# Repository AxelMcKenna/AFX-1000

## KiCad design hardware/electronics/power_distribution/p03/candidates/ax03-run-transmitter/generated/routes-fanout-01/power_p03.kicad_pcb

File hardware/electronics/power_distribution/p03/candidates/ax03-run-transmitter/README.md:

# P03 AX03 RUN transmitter candidate

The preferred 264-part paired project has zero native DRC errors, warnings,
opens, ERC and parity findings with every rule category enabled. It is not
physically qualified or released for fabrication.

Use [CURRENT_LAYOUT.json](CURRENT_LAYOUT.json) or the
[checked project](generated/native-closed-transmitter/power_p03.kicad_pro).
The root PCB is an incomplete staging parent.

The [integration review](../../../../../qualification/boards/aux_low_power_run/P03_INTEGRATION_REVIEW.md)
documents exact source conservation, actual local bypass paths, five new
via-in-SMD process requirements, the four-wire logical E28 map and outstanding
qualification. The
[actual PCB plot](generated/native-closed-transmitter/closed-top.svg),
[native results](generated/native-closed-transmitter/review.json) and
[handoff](generated/native-closed-transmitter/handoff.json) retain the evidence.

The eight-part source cell buffers only J106.3. Original R113, internal RUN/PG
and switch topology remain intact. The original 160 × 45 mm outline, mounting
positions, stackup and all 1,254 strict-source vias remain exact. The strict
source's two P19_SRC neck limitations and all manufacturing/physical holds carry
forward. Canonical and preserved source projects are unchanged.

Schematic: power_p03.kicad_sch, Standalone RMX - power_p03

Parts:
C1, C63: 10uF 63V X7R; C_1210_3225Metric
C2, C3, C5, C6, C8, C9, C37, C42, C52, C57, C64, C65, C67, C68, C70, C204, C205, C224, C225, C254: 22uF 50V X7R 20% TDK C3225X7R1H226M250AC; C_1210_3225Metric
C4, C7, C10, C35, C38, C40, C43, C50, C53, C55, C58, C59, C61, C66, C69, C71: 100nF 50V X7R; C_0805_2012Metric
C11, C30, C107, C108: 100nF 16V X7R; C_0805_2012Metric
C12, C14, C73, C75: 68pF 50V C0G 5%; C_0805_2012Metric
C13, C15, C74, C76: 330nF 16V X7R; C_0805_2012Metric
C31: 2.2uF 16V X7R; C_0805_2012Metric
C32, C33: 1uF film 63V 10% MKS2C041001F00KSSD; C_Rect_L7.2mm_W5.0mm_P5.00mm
C34, C39, C49, C54, C240: 47nF 50V C0G 5%; C_1210_3225Metric
C36, C41, C51, C56: 10uF 50V X7R; C_1210_3225Metric
C60, C62, C105: 1uF 50V X7R; C_0805_2012Metric
C72, C210, C211, C230, C231: 100nF 50V X7R 10% TDK C1005X7R1H104K050BB; C_0402_1005Metric
C101, C102: 2.2uF 100V X7R; C_1210_3225Metric
C103: 220uF 35V electrolytic 20% (EEUFR1V221); CP_Radial_D8.0mm_P3.50mm
C104: 1uF 50V X7R; C_1210_3225Metric
C106: 10uF 25V X7R 10% TDK C3225X7R1E106K250AC; C_1210_3225Metric
C109: 1nF 16V C0G 5%; C_0805_2012Metric
C110: 10nF 25V C0G 5% KEMET C0603C103J3GACTU; C_0603_1608Metric
C113: 1uF 100V X7S 10% TDK C2012X7S2A105K125AE; C_0805_2012Metric
C200, C220: 4.7uF 25V X7R 10% TDK C2012X7R1E475K125AB; C_0805_2012Metric
C201, C221, C255, C301, C302: 100nF 50V X7R; C_0603_1608Metric
C202, C203, C222, C223: 2.2uF 50V X7R 10% TDK C2012X7R1H225K125AC; C_0805_2012Metric
C206, C207, C208, C209, C226, C227, C228, C229: 47uF 25V X7S 20% TDK C3225X7S1E476M250AC; C_1210_3225Metric
C241: 1uF 25V X7R; C_1210_3225Metric
C242, C243, C244, C245, C246, C247, C248, C249, C250, C251: 100nF 25V C0G 5% KEMET C1206C104J3GACTU; C_1206_3216Metric
C252, C253: 1uF 16V X7R; C_1210_3225Metric
C300: 10nF 50V C0G 5%; C_0805_2012Metric
C401, C402: 100nF 50V X7R C0603C104K5RACTU; C0603
C403: 10nF 50V C0G C0603C103J5GACTU; C0603
D1, D2, D3, D4, D103: SS16-E3/61T; D_SMA
D101: SMBJ33CA-E3/52; D_SMB
D102: BAS116,215; SOT-23
J2: Header6; PinHeader_1x06_P2.54mm_Vertical
J3: Header2; PinHeader_1x02_P2.54mm_Vertical
J20, J21, J23, J24: Wurth 7466003R M3 SMT; Wurth_7466003R
J22: P03 READY test; PinHeader_1x03_P2.54mm_Vertical
J101: JST B2PS-VH (VHR-2N/SVH-41T-P1.1 AWG16); JST_VH_B2PS-VH_1x02_P3.96mm_Horizontal
J103: Bare POWER_READY probe pads, no fitted header; Probe2_P2.54_D1
J104: JST B3B-XH-A (XHP-3/SXH-001T-P0.6); JST_XH_B3B-XH-A_1x03_P2.50mm_Vertical
J106: JST B4B-XH-A (XHP-4/SXH-001T-P0.6); JST_XH_B4B-XH-A_1x04_P2.50mm_Vertical
L1, L6: 33uH 20% SRP7050WA-330M; SRP7050WA
L2, L3, L7, L8: 68uH 20% SRP1050WA-680M; SRP1050WA
L20, L23: 4.7uH 20% Coilcraft XAL7030-472MEC; L_Coilcraft_XAL7030-472
Q101: PSMN012-100YL,115; LFPAK56
Q102: BSS138-7-F; SOT-23
Q103: DMN2056U-7; SOT-23
R1: 300k 0.01% 5ppm; R_0805_2012Metric
R2, R3, R4, R45, R46: 15k 0.01% 5ppm; R_0805_2012Metric
R5, R20, R21, R34, R35: 330k 0.01% 5ppm; R_0805_2012Metric
R6, R7, R49, R50: 4.7k 1%; R_0805_2012Metric
R17, R19, R110: 1k 1%; R_0805_2012Metric
R18, R120: 100k 1%; R_0805_2012Metric
R22, R27, R36, R41, R243, R244: 100k 0.01% 5ppm; R_0805_2012Metric
R23, R28, R37, R42, R241: 6.8k 1%; R_0805_2012Metric
R24, R38: 9.09k 1%; R_0805_2012Metric
R25, R39, R47, R306: 200k 0.01% 5ppm; R_0805_2012Metric
R26, R40, R308: 180k 0.01% 5ppm; R_0805_2012Metric
R29, R43: 5.62k 1%; R_0805_2012Metric
R44: 240k 0.01% 5ppm; R_0805_2012Metric
R48, R301, R303, R305, R307, R309, R314: 10k 0.01% 5ppm; R_0805_2012Metric
R101, R103, R117: 309k 0.1% 10ppm; R_0805_2012Metric
R102: 40.2k 0.1% 10ppm; R_0805_2012Metric
R104: 28k 0.1% 10ppm; R_0805_2012Metric
R105: 68.1k 0.1% 10ppm; R_0805_2012Metric
R106, R109, R118, R119: 10k 0.1% 10ppm; R_0805_2012Metric
R107: 4.02k 0.1% 10ppm; R_0805_2012Metric
R108: 11.7k 0.1% 10ppm; R_0805_2012Metric
R111, R204, R224, R246: 10k 1%; R_0805_2012Metric
R112, R114: 47k 1%; R_0805_2012Metric
R113: 3.3k 1%; R_0805_2012Metric
R115: 30.9k 0.1% 10ppm; R_0805_2012Metric
R116: 3.09k 0.1% 10ppm; R_0805_2012Metric
R121: 100 1%; R_0805_2012Metric
R130: 49.9 0.01% 5ppm; R_0805_2012Metric
R200: 9k 0.01% 2ppm Susumu RG2012L-902-L-T1; R_0805_2012Metric
R201: 1k 0.01% 2ppm Susumu RG2012L-102-L-T1; R_0805_2012Metric
R202, R222: 24.3k 1%; R_0805_2012Metric
R203, R223: 18.2k 0.1% 25ppm Panasonic ERA6AEB1822V; R_0805_2012Metric
R205, R225: 22k 1%; R_0805_2012Metric
R206: 54.9 0.1% 25ppm Panasonic ERA6AEB549V; R_0805_2012Metric
R220: 11k 0.01% 5ppm; R_0805_2012Metric
R221, R311: 1k 0.01% 5ppm; R_0805_2012Metric
R240: 100 0.01% 5ppm; R_0805_2012Metric
R242: 120 0.01% 5ppm; R_0805_2012Metric
R245: 2.21k 1%; R_0805_2012Metric
R300, R302: 87.6k 0.01% 5ppm; R_0805_2012Metric
R304: 324k 0.01% 5ppm; R_0805_2012Metric
R310: 590 0.01% 5ppm; R_0805_2012Metric
R312: 7.5k 0.01% 5ppm; R_0805_2012Metric
R313: 1M 0.01% 5ppm; R_0805_2012Metric
R315: 750k 0.01% 5ppm; R_0805_2012Metric
R316: 2.2k 0.1% 25ppm Panasonic ERA6AEB222V; R_0805_2012Metric
R401: 100k ohm TNPW0805100KBEEA; R0805
R402: 10M 1% CRCW080510M0FKEA; R0805
R403: 1k 1% CRCW12061K00FKEA; R1206
U1, U13: LT3471EDD#PBF; DFN-10-1EP_3x3mm_P0.5mm_EP1.65x2.38mm
U4: REF5025EIDR; SOIC-8_3.9x4.9mm_P1.27mm
U5: OPA4192ID; SOIC-14_3.9x8.7mm_P1.27mm
U6, U24: OPA2192ID; SOIC-8_3.9x4.9mm_P1.27mm
U7: LT3080IMS8E#PBF; MSOP-8-1EP_3x3mm_P0.65mm_EP1.68x1.88mm
U8: LT3080IQ#PBF; TO-263-5_TabPin3
U10, U11: LT3090IDD#PBF; DFN-10-1EP_3x3mm_P0.5mm_EP1.65x2.38mm
U12: LT1634AIS8-2.5#PBF; SOIC-8_3.9x4.9mm_P1.27mm
U20, U23: TPS543620RPYR; TPS543620_RPY0014A
U21: ADR4550BRZ; SOIC-8_3.9x4.9mm_P1.27mm
U22: LT3045IDD#PBF; DFN-10-1EP_3x3mm_P0.5mm_EP1.65x2.38mm
U25: LTC2910HGN#PBF; SSOP-16_3.9x4.9mm_P0.635mm
U26: SN74LVC1G97DBVR; SOT-23-6
U101: TPS26630RGER; Texas_RGE0024H_VQFN-24-1EP_4x4mm_P0.5mm_EP2.7x2.7mm
U102: TPS7A1601DGNR; MSOP-8-1EP_3x3mm_P0.65mm_EP1.68x1.88mm
U103: TLV7011DBVR; SOT-23-5
U201: TPS389001DSET; TI_DSE0006A
U202: SN74AUP1G17DCKR; TI_DCK0005A

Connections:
/5V_DIG_SRC: C30.1, C206.1 (+), C207.1 (+), C208.1 (+), C209.1 (+), J3.1 (5V_DIG), J23.1, L20.2 (OUT), R6.1, R7.1, R49.1, R50.1, R200.1, R300.1, U4.1 (EN), U4.2 (VIN), U10.5 (SHDN), U11.5 (SHDN)
/AGND: C2.2, C3.2, C4.2, C5.2, C6.2, C7.2, C8.2, C9.2, C10.2, C11.2, C13.2, C15.2, C30.2, C31.2, C32.2, C33.2, C35.2, C36.2, C37.2, C38.2, C40.2, C41.2, C42.2, C43.2, C50.2, C51.2, C52.2, C53.2, C55.2, C56.2, C57.2, C58.2, C59.2, C60.2, C61.2, C62.2, C64.2, C65.2, C66.2, C67.2, C68.2, C69.2, C70.2, C71.2, C72.2, C74.2, C76.2, C101.2 (-), C102.2 (-), C103.2 (-), C104.2 (-), C105.2 (-), C106.2 (-), C107.2 (-), C108.2 (-), C109.2 (-), C110.2 (-), C113.2 (-), C200.2 (-), C202.2 (-), C203.2 (-), C204.2 (-), C205.2 (-), C206.2 (-), C207.2 (-), C208.2 (-), C209.2 (-), C210.2 (-), C211.2 (-), C220.2 (-), C222.2 (-), C223.2 (-), C224.2 (-), C225.2 (-), C226.2 (-), C227.2 (-), C228.2 (-), C229.2 (-), C230.2 (-), C231.2 (-), C241.2 (-), C242.2 (-), C243.2 (-), C244.2 (-), C245.2 (-), C246.2 (-), C247.2 (-), C248.2 (-), C249.2 (-), C250.2 (-), C251.2 (-), C252.2 (-), C253.2 (-), C254.2 (-), C255.2 (-), C300.2 (-), C301.2 (-), C302.2 (-), C401.2, C402.2, C403.2, D2.1 (K), D4.1 (K), D101.2, D103.2 (ANODE), J2.2 (AGND), J3.2 (AGND), J20.1, J21.1, J22.2 (AGND), J101.2 (AGND), J103.1 (AGND), J104.3 (AGND), J106.2 (AGND), Q103.2 (SOURCE), R3.2, R22.2, R24.2, R27.2, R29.2, R36.2, R38.2, R41.2, R43.2, R45.2, R102.2, R104.2, R106.2, R107.2, R109.2, R111.2, R112.2, R114.2, R116.2, R119.2, R120.2, R201.2, R202.2, R203.2, R205.2, R221.2, R222.2, R223.2, R225.2, R243.2, R245.2, R301.2, R303.2, R305.2, R307.2, R309.2, R311.2, R402.2, U1.5 (FB2N), U1.11 (GND_EP), U4.4 (GND), U5.10 (+), U5.11 (V-), U5.12 (SPARE+), U6.8 (V+), U10.3 (GND), U11.3 (GND), U12.6 (VOUT/CATHODE), U13.5 (FB2N), U13.11 (GND_EP), U20.5 (AGND), U20.9 (PGND), U20.11 (PGND), U21.4 (GND), U22.5 (ILIM), U22.8 (GND), U22.11 (EP_GND), U23.5 (AGND), U23.9 (PGND), U23.11 (PGND), U24.4 (V_N), U24.5 (IN_B_P), U25.9 (GND), U25.13 (DIS), U25.14 (SEL), U26.1 (In1_AND_CONFIG_LOW), U26.2 (GND), U101.8 (GND), U101.25 (EP/GND), U102.4 (GND), U102.9 (EP/GND), U103.2 (VEE), U201.2 (GND), U202.3 (GND)
/AUX_FB: R109.1, R130.2, U102.2 (FB)
/AUX_START_DELAY: C110.1 (+), U102.7 (DELAY)
/AX03_RUN_DRIVE: R403.1, U202.4 (Y)
/AX03_SOURCE_CT: C403.1, U201.5 (CT)
/AX03_SOURCE_RESET: R401.2, R402.1, U201.6 (RESET_N), U202.2 (A)
/BLOCK_DRV: Q102.1 (GATE), U101.4 (DRV)
/BLOCK_GATE: Q101.4 (GATE), Q102.3 (DRAIN), U101.3 (B_GATE)
/CUK_NODE: C1.2, D2.2 (A), L3.1
/DC_IN: C101.1 (+), D101.1, J101.1 (DC_IN), Q101.1 (SOURCE), Q101.2 (SOURCE), Q101.3 (SOURCE), Q102.2 (SOURCE), R101.1, R103.1, U101.5 (IN_SYS)
/FAST_OV_GATE: Q103.1 (GATE), R120.1, R121.2
/FAST_OV_OUT: R117.1, R121.1, U103.1 (OUT)
/FAST_OV_REF: C109.1 (+), R118.2, R119.1, U103.4 (IN-)
/FAST_OV_SENSE: R115.2, R116.1, R117.2, U103.3 (IN+)
/INPUT_ILIM: R107.1, U101.10 (ILIM)
/INPUT_OV: D102.1 (ANODE), R103.2, R104.1, U101.7 (OVP)
/INPUT_PGTH: R105.2, R106.1, U101.15 (PGTH)
/INPUT_SLEW: C105.1 (+), U101.9 (dVdT)
/INPUT_UV: R101.2, R102.1, U101.6 (UVLO)
/LO_CUK_NODE: C63.2, D4.2 (A), L8.1
/LO_N_FB: C75.2, R46.2, R47.1, U13.4 (FB2P)
/LO_N_RMID: R47.2, R48.1
/LO_N_SS: C76.1, R50.2, U13.7 (SHDN_SS2)
/LO_N_SW: C63.1, L7.2, U13.6 (SW2)
/LO_P_FB: C73.2, R44.2, R45.1, U13.1 (FB1N)
/LO_P_SS: C74.1, R49.2, U13.9 (SHDN_SS1)
/LO_P_SW: D3.2 (A), L6.2, U13.10 (SW1)
/LO_REF_1V: C72.1, R46.1, U13.2 (FB1P), U13.3 (VREF)
/N12_DRIVE: C54.1, R42.1, U6.7 (OUT)
/N12_FB: C54.2, R40.2, R41.1, U6.6 (-)
/N12_RMID: R39.2, R40.1
/N12_SET: C55.1, R39.1, R42.2, U11.4 (SET)
/N12_SRC: C57.1, C58.1, J2.5 (N12), R43.1, R315.2, U11.1 (OUT), U11.2 (OUT)
/N19_DRIVE: C49.1, R37.1, U6.1 (OUT)
/N19_FB: C49.2, R35.2, R36.1, U6.2 (-)
/N19_RMID: R34.2, R35.1
/N19_SET: C50.1, R34.1, R37.2, U10.4 (SET)
/N19_SRC: C52.1, C53.1, J2.3 (N19), R38.1, R313.2, U10.1 (OUT), U10.2 (OUT)
/NREF_2V5: R18.1, R19.1, U12.4 (GND/ANODE), U12.5 (TEST)
/NREF_FILTER: C33.1, R19.2, U6.3 (+), U6.5 (+)
/P03_ALL_SOURCES_READY: J22.1 (ALL_SOURCES_READY), J106.4 (SOURCE_READY), R316.2, U25.12 (RST_ACTIVE_LOW)
/P03_ANA_DIV: R242.2, R243.1, R244.1
/P03_ANA_DRIVE: C240.1 (+), R241.1, U24.1 (OUT_A)
/P03_ANA_FB: C240.2 (-), R244.2, U24.2 (IN_A_N)
/P03_ANA_SET: C241.1 (+), R241.2, R242.1, U22.7 (SET)
/P03_AUX_TRIM: R108.2, R130.1
/P03_A_BOOT: C221.1 (+), U23.14 (BOOT)
/P03_A_BP5: C220.1 (+), U23.6 (BP5)
/P03_A_ENABLE: R224.2, R225.1, U23.7 (EN)
/P03_A_FB: R220.2, R221.1, U23.4 (FB)
/P03_A_FSEL: R222.1, U23.1 (SYNC_FSEL)
/P03_A_MODE: R223.1, U23.2 (MODE)
/P03_A_SW: C221.2 (-), L23.1 (SW), U23.10 (SW), U23.13 (SW_BOOT_RETURN)
/P03_D_BOOT: C201.1 (+), U20.14 (BOOT)
/P03_D_BP5: C200.1 (+), U20.6 (BP5)
/P03_D_ENABLE: R204.2, R205.1, U20.7 (EN)
/P03_D_FB: R201.1, R206.2, U20.4 (FB)
/P03_D_FB_TRIM: R200.2, R206.1
/P03_D_FSEL: R202.1, U20.1 (SYNC_FSEL)
/P03_D_MODE: R203.1, U20.2 (MODE)
/P03_D_SW: C201.2 (-), L20.1 (SW), U20.10 (SW), U20.13 (SW_BOOT_RETURN)
/P03_MON_ANA: R302.2, R303.1, U25.2 (V2)
/P03_MON_BUCK_OK: U25.5 (V5), U26.4 (Y)
/P03_MON_DIG: R300.2, R301.1, U25.1 (V1)
/P03_MON_N12: R314.2, R315.1, U25.8 (V8)
/P03_MON_N19: R312.2, R313.1, U25.7 (V7)
/P03_MON_NEG_BIAS: R310.2, R311.1, R312.1, R314.1
/P03_MON_P12: R306.2, R307.1, U25.4 (V4)
/P03_MON_P19: R304.2, R305.1, U25.3 (V3)
/P03_MON_REF: R310.1, U25.10 (REF)
/P03_MON_TIMER: C300.1 (+), U25.15 (TMR)
/P03_MON_VIN: R308.2, R309.1, U25.6 (V6)
/P03_PRE6V: C226.1 (+), C227.1 (+), C228.1 (+), C229.1 (+), C253.1 (+), L23.2 (OUT), R220.1, U21.2 (VIN), U22.1 (IN), U22.2 (IN), U22.3 (EN_UV), U22.6 (PGFB)
/P03_REF5: C252.1 (+), R240.1, U21.6 (VOUT)
/P03_REF_FILTER: C242.1 (+), C243.1 (+), C244.1 (+), C245.1 (+), C246.1 (+), C247.1 (+), C248.1 (+), C249.1 (+), C250.1 (+), C251.1 (+), R240.2, U24.3 (IN_A_P)
/P03_SOURCES_READY: R246.2, U20.3 (PGOOD), U23.3 (PGOOD), U26.3 (In0)
/P03_SPARE_24: U24.6 (IN_B_N), U24.7 (OUT_B)
/P03_SPARE_C: U5.8 (OUT), U5.9 (-)
/P12_DRIVE: C39.1, R28.1, U5.7 (OUT)
/P12_FB: C39.2, R26.2, R27.1, U5.6 (-)
/P12_RMID: R25.2, R26.1
/P12_SET: C40.1, R25.1, R28.2, U8.2 (SET)
/P12_SRC: C42.1, C43.1, J2.4 (P12), R29.1, R306.1, U8.3 (OUT/TAB)
/P19_DRIVE: C34.1, R23.1, U5.1 (OUT)
/P19_FB: C34.2, R21.2, R22.1, U5.2 (-)
/P19_RMID: R20.2, R21.1
/P19_SET: C35.1, R20.1, R23.2, U7.4 (SET)
/P19_SRC: C37.1, C38.1, J2.1 (P19), R24.1, R304.1, U7.1 (OUT), U7.2 (OUT), U7.3 (OUT), U7.9 (EP/OUT)
/POWER_READY: J22.3 (POWER_READY), J103.2 (POWER_READY), R110.2, R204.1, R224.1, U26.6 (In2), U101.16 (PGOOD)
/POWER_RUN: J104.2 (POWER_RUN), Q103.3 (DRAIN), R112.1, U101.12 (SHDN), U102.3 (PG), U201.1 (SENSE)
/POWER_RUN_E28_LEAF: J106.3 (POWER_RUN), R403.2
/PREF_2V5: C31.1, R17.1, U4.6 (VOUT)
/PREF_FILTER: C32.1, R17.2, U5.3 (+), U5.5 (+)
/RAW_N17: C56.1, C67.1, C68.1, C69.1, C75.1, L8.2, R48.2, U11.8 (ILIM), U11.9 (IN), U11.10 (IN), U11.11 (EP/IN)
/RAW_N22: C8.1, C9.1, C10.1, C14.1, C51.1, C61.1, C62.1, L3.2, R5.2, R18.2, U6.4 (V-), U10.8 (ILIM), U10.9 (IN), U10.10 (IN), U10.11 (EP/IN)
/RAW_N_FB: C14.2, R4.2, R5.1, U1.4 (FB2P)
/RAW_N_SS: C15.1, R7.2, U1.7 (SHDN_SS2)
/RAW_N_SW: C1.1, L2.2, U1.6 (SW2)
/RAW_P17: C41.1, C64.1, C65.1, C66.1, C73.1, D3.1 (K), R44.1, U8.4 (VCONTROL), U8.5 (IN)
/RAW_P22: C5.1, C6.1, C7.1, C12.1, C36.1, C59.1, C60.1, D1.1 (K), R1.1, U5.4 (V+), U7.5 (VCONTROL), U7.7 (IN), U7.8 (IN)
/RAW_P_FB: C12.2, R2.2, R3.1, U1.1 (FB1N)
/RAW_P_RMID: R1.2, R2.1
/RAW_P_SS: C13.1, R6.2, U1.9 (SHDN_SS1)
/RAW_P_SW: D1.2 (A), L1.2, U1.10 (SW1)
/SPARE_OUT: U5.13 (SPARE-), U5.14 (SPARE_OUT)
/SWITCH_SUPPLY: J104.1 (SWITCH_SUPPLY), R113.2
/SW_REF_1V: C11.1, R4.1, U1.2 (FB1P), U1.3 (VREF)
/V2V5_AUX: C106.1 (+), C107.1 (+), C108.1 (+), C301.1 (+), C302.1 (+), C401.1, C402.1, D102.3 (CATHODE), J106.1 (V2V5_AUX), R108.1, R110.1, R111.1, R113.1, R118.1, R246.1, R316.1, R401.1, U25.16 (VCC), U26.5 (VCC), U102.1 (OUT), U103.5 (VCC), U201.3 (MR), U201.4 (VDD), U202.5 (VCC)
/V5_REG_SRC: C254.1 (+), J2.6 (V5_REG), J24.1, R245.1, R302.1, U22.9 (OUTS), U22.10 (OUT)
/VIN_IC: C102.1 (+), C113.1 (+), Q101.5 (DRAIN/MB), R115.1, U101.1 (IN), U101.2 (IN), U102.5 (EN), U102.8 (IN)
/VIN_PROTECTED: C2.1, C3.1, C4.1, C70.1, C71.1, C103.1 (+), C104.1 (+), C202.1 (+), C203.1 (+), C204.1 (+), C205.1 (+), C210.1 (+), C211.1 (+), C222.1 (+), C223.1 (+), C224.1 (+), C225.1 (+), C230.1 (+), C231.1 (+), C255.1 (+), D103.1 (CATHODE), L1.1, L2.1, L6.1, L7.1, R105.1, R114.1, R308.1, U1.8 (VIN), U13.8 (VIN), U20.8 (VIN), U20.12 (VIN), U23.8 (VIN), U23.12 (VIN), U24.8 (V_P), U101.17 (OUT), U101.18 (OUT)

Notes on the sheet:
AX03 prototype: only J106.3 buffered; internal POWER_RUN, R113 and PG topology retained. No physical/fabrication release.

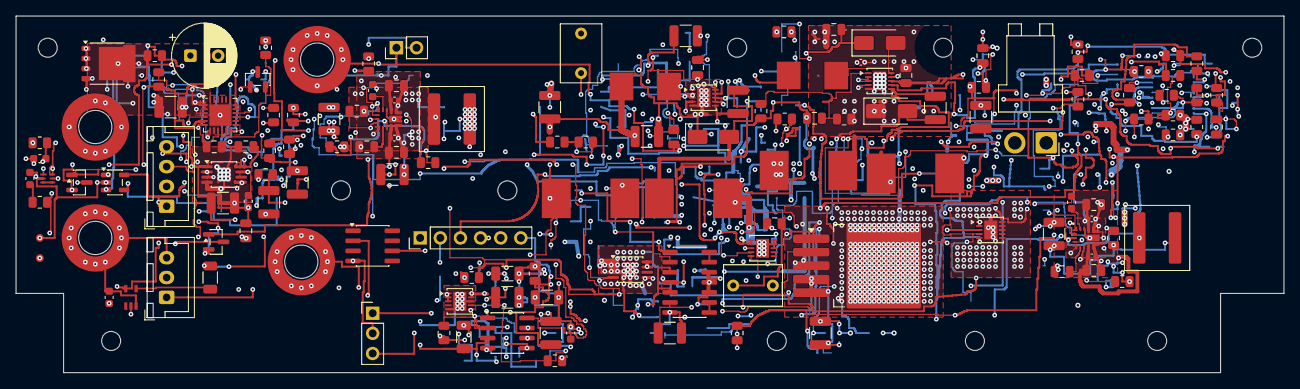
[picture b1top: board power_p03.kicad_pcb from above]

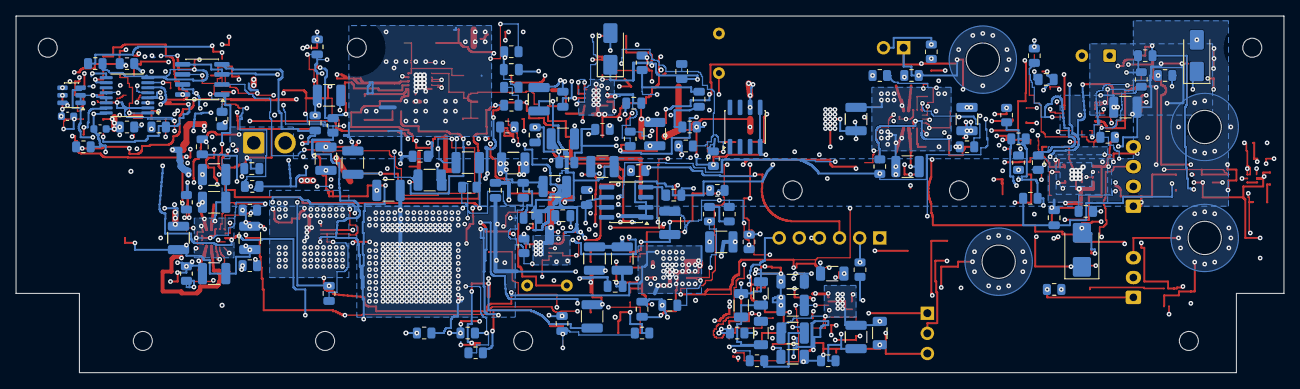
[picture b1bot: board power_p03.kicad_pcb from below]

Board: 6 copper layers, 160.0 x 45.0 mm, 274 parts (125 on the bottom side), 112 nets.

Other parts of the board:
H1, H2, H3, H4, H5, H6, H7, H8, H9, H10: M2_CLEARANCE; M2_Clearance

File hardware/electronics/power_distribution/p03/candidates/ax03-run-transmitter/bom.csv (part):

Reference,Part_or_value,Footprint,Source,Note
U1,LT3471EDD#PBF,Package_DFN_QFN:DFN-10-1EP_3x3mm_P0.5mm_EP1.65x2.38mm,https://www.analog.com/media/en/technical-documentation/data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,"EP is ground. Switches rated42V; raw rails are nominal+/-22V, subject to allocated error/ripple. P03 symbol erratum per LT3471 RevC page4:pin5 is quiet FB2N, not PGND; EP11 is the sole power ground. Native pin/net mapping preserved."
L1,33uH 20% SRP7050WA-330M,RMX_P03:SRP7050WA,https://www.bourns.com/docs/Product-Datasheets/SRP7050WA.pdf,"E24 selected candidate; retain requirement 33uH 20% Isat>=3A Irms>=1.5A DCR<=0.2ohm. Datasheet Irms/Isat are typical25C entries, not guaranteed minimums; bias, hot DCR, core loss and actual temperature qualification remain open."
L2,68uH 20% SRP1050WA-680M,RMX_P03:SRP1050WA,https://www.bourns.com/docs/Product-Datasheets/SRP1050WA.pdf,"E24 selected candidate; retain requirement 68uH 20% Isat>=3A Irms>=1.5A DCR<=0.2ohm. Datasheet Irms/Isat are typical25C entries, not guaranteed minimums; bias, hot DCR, core loss and actual temperature qualification remain open."
L3,68uH 20% SRP1050WA-680M,RMX_P03:SRP1050WA,https://www.bourns.com/docs/Product-Datasheets/SRP1050WA.pdf,"E24 selected candidate; retain requirement 68uH 20% Isat>=3A Irms>=1.5A DCR<=0.2ohm. Datasheet Irms/Isat are typical25C entries, not guaranteed minimums; bias, hot DCR, core loss and actual temperature qualification remain open."
D1,SS16-E3/61T,Diode_SMD:D_SMA,https://www.vishay.com/docs/88746/ss12.pdf,Vishay60V1A; VF allowance1V includes cold margin; actual leakage/ripple and ringing require qualification.
D2,SS16-E3/61T,Diode_SMD:D_SMA,https://www.vishay.com/docs/88746/ss12.pdf,Vishay60V1A; VF allowance1V includes cold margin; actual leakage/ripple and ringing require qualification.
C1,10uF 63V X7R,Capacitor_SMD:C_1210_3225Metric,,Effective>=2.2uF; RMS ripple>=0.6A required at switching frequency
C2,22uF 50V X7R 20% TDK C3225X7R1H226M250AC,Capacitor_SMD:C_1210_3225Metric,https://product.tdk.com/en/search/capacitor/ceramic/mlcc/inf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,Each effective>=5uF; capacitor RMS/ESR and placement require qualification Exact TDK bulk candidate:2.80mm maximum body +0.10mm seat; effective capacitance/ripple/aging and native IPC1210 land versus manufacturer recommendation require approval. Catalog plots are reference-only.
C3,22uF 50V X7R 20% TDK C3225X7R1H226M250AC,Capacitor_SMD:C_1210_3225Metric,https://product.tdk.com/en/search/capacitor/ceramic/mlcc/inf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,Each effective>=5uF; capacitor RMS/ESR and placement require qualification Exact TDK bulk candidate:2.80mm maximum body +0.10mm seat; effective capacitance/ripple/aging and native IPC1210 land versus manufacturer recommendation require approval. Catalog plots are reference-only.
C4,100nF 50V X7R,Capacitor_SMD:C_0805_2012Metric,,
C5,22uF 50V X7R 20% TDK C3225X7R1H226M250AC,Capacitor_SMD:C_1210_3225Metric,https://product.tdk.com/en/search/capacitor/ceramic/mlcc/inf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,Each effective>=5uF; capacitor RMS/ESR and placement require qualification Exact TDK bulk candidate:2.80mm maximum body +0.10mm seat; effective capacitance/ripple/aging and native IPC1210 land versus manufacturer recommendation require approval. Catalog plots are reference-only.
C6,22uF 50V X7R 20% TDK C3225X7R1H226M250AC,Capacitor_SMD:C_1210_3225Metric,https://product.tdk.com/en/search/capacitor/ceramic/mlcc/inf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,Each effective>=5uF; capacitor RMS/ESR and placement require qualification Exact TDK bulk candidate:2.80mm maximum body +0.10mm seat; effective capacitance/ripple/aging and native IPC1210 land versus manufacturer recommendation require approval. Catalog plots are reference-only.
C7,100nF 50V X7R,Capacitor_SMD:C_0805_2012Metric,,
C8,22uF 50V X7R 20% TDK C3225X7R1H226M250AC,Capacitor_SMD:C_1210_3225Metric,https://product.tdk.com/en/search/capacitor/ceramic/mlcc/inf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,Each effective>=5uF; capacitor RMS/ESR and placement require qualification Exact TDK bulk candidate:2.80mm maximum body +0.10mm seat; effective capacitance/ripple/aging and native IPC1210 land versus manufacturer recommendation require approval. Catalog plots are reference-only.
C9,22uF 50V X7R 20% TDK C3225X7R1H226M250AC,Capacitor_SMD:C_1210_3225Metric,https://product.tdk.com/en/search/capacitor/ceramic/mlcc/inf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,Each effective>=5uF; capacitor RMS/ESR and placement require qualification Exact TDK bulk candidate:2.80mm maximum body +0.10mm seat; effective capacitance/ripple/aging and native IPC1210 land versus manufacturer recommendation require approval. Catalog plots are reference-only.
C10,100nF 50V X7R,Capacitor_SMD:C_0805_2012Metric,,
C11,100nF 16V X7R,Capacitor_SMD:C_0805_2012Metric,,
R1,300k 0.01% 5ppm,Resistor_SMD:R_0805_2012Metric,,
R2,15k 0.01% 5ppm,Resistor_SMD:R_0805_2012Metric,,
R3,15k 0.01% 5ppm,Resistor_SMD:R_0805_2012Metric,,
R4,15k 0.01% 5ppm,Resistor_SMD:R_0805_2012Metric,,
R5,330k 0.01% 5ppm,Resistor_SMD:R_0805_2012Metric,,
C12,68pF 50V C0G 5%,Capacitor_SMD:C_0805_2012Metric,,Initial compensation candidate; manufacturer-model/load-step loop qualification open
R6,4.7k 1%,Resistor_SMD:R_0805_2012Metric,,
C13,330nF 16V X7R,Capacitor_SMD:C_0805_2012Metric,,
C14,68pF 50V C0G 5%,Capacitor_SMD:C_0805_2012Metric,,Initial compensation candidate; manufacturer-model/load-step loop qualification open
R7,4.7k 1%,Resistor_SMD:R_0805_2012Metric,,
C15,330nF 16V X7R,Capacitor_SMD:C_0805_2012Metric,,
U4,REF5025EIDR,Package_SO:SOIC-8_3.9x4.9mm_P1.27mm,https://www.ti.com/lit/ds/symlink/ref50.pdf,
C30,100nF 16V X7R,Capacitor_SMD:C_0805_2012Metric,,
C31,2.2uF 16V X7R,Capacitor_SMD:C_0805_2012Metric,,Effective>=1uF
R17,1k 1%,Resistor_SMD:R_0805_2012Metric,,
C32,1uF film 63V 10% MKS2C041001F00KSSD,Capacitor_THT:C_Rect_L7.2mm_W5.0mm_P5.00mm,https://www.wima.de/wp-content/uploads/media/d_WIMA_MKS_2.pdf,"E24 candidate WIMA MKS2, 1uF63V10%, body7.2x5x10mm/pitch5mm; leakage/assembly qualification open."
U12,LT1634AIS8-2.5#PBF,Package_SO:SOIC-8_3.9x4.9mm_P1.27mm,https://www.analog.com/media/en/technical-documentation/data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,Industrial A grade. Do not connect pin4 to system ground.
R18,100k 1%,Resistor_SMD:R_0805_2012Metric,,
R19,1k 1%,Resistor_SMD:R_0805_2012Metric,,
C33,1uF film 63V 10% MKS2C041001F00KSSD,Capacitor_THT:C_Rect_L7.2mm_W5.0mm_P5.00mm,https://www.wima.de/wp-content/uploads/media/d_WIMA_MKS_2.pdf,"E24 candidate WIMA MKS2, 1uF63V10%, body7.2x5x10mm/pitch5mm; leakage/assembly qualification open."
R20,330k 0.01% 5ppm,Resistor_SMD:R_0805_2012Metric,,
R21,330k 0.01% 5ppm,Resistor_SMD:R_0805_2012Metric,,
R22,100k 0.01% 5ppm,Resistor_SMD:R_0805_2012Metric,,
R23,6.8k 1%,Resistor_SMD:R_0805_2012Metric,,Limit SET clamp current; Kelvin DC feedback is after this resistor
C34,47nF 50V C0G 5%,Capacitor_SMD:C_1210_3225Metric,,Local HF feedback bypasses remote SET pole; finite loop/PCB qualification open
C35,100nF 50V X7R,Capacitor_SMD:C_0805_2012Metric,,Effective50..120nF for target-source loop screen
R24,9.09k 1%,Resistor_SMD:R_0805_2012Metric,,Minimum-load/discharge resistor; qualify power rating and thermal derating
U7,LT3080IMS8E#PBF,Package_SO:MSOP-8-1EP_3x3mm_P0.65mm_EP1.68x1.88mm,https://www.analog.com/media/en/technical-documentation/data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,"EP is OUT, not ground. Separate IN/VCONTROL dropout checks required."
C36,10uF 50V X7R,Capacitor_SMD:C_1210_3225Metric,,Effective>=5uF at worst bias/temperature
C37,22uF 50V X7R 20% TDK C3225X7R1H226M250AC,Capacitor_SMD:C_1210_3225Metric,https://product.tdk.com/en/search/capacitor/ceramic/mlcc/inf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,Effective>=10uF; actual ESR/transient stability pending Exact TDK bulk candidate:2.80mm maximum body +0.10mm seat; effective capacitance/ripple/aging and native IPC1210 land versus manufacturer recommendation require approval. Catalog plots are reference-only.
C38,100nF 50V X7R,Capacitor_SMD:C_0805_2012Metric,,
R25,200k 0.01% 5ppm,Resistor_SMD:R_0805_2012Metric,,
R26,180k 0.01% 5ppm,Resistor_SMD:R_0805_2012Metric,,
R27,100k 0.01% 5ppm,Resistor_SMD:R_0805_2012Metric,,
R28,6.8k 1%,Resistor_SMD:R_0805_2012Metric,,Limit SET clamp current; Kelvin DC feedback is after this resistor
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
